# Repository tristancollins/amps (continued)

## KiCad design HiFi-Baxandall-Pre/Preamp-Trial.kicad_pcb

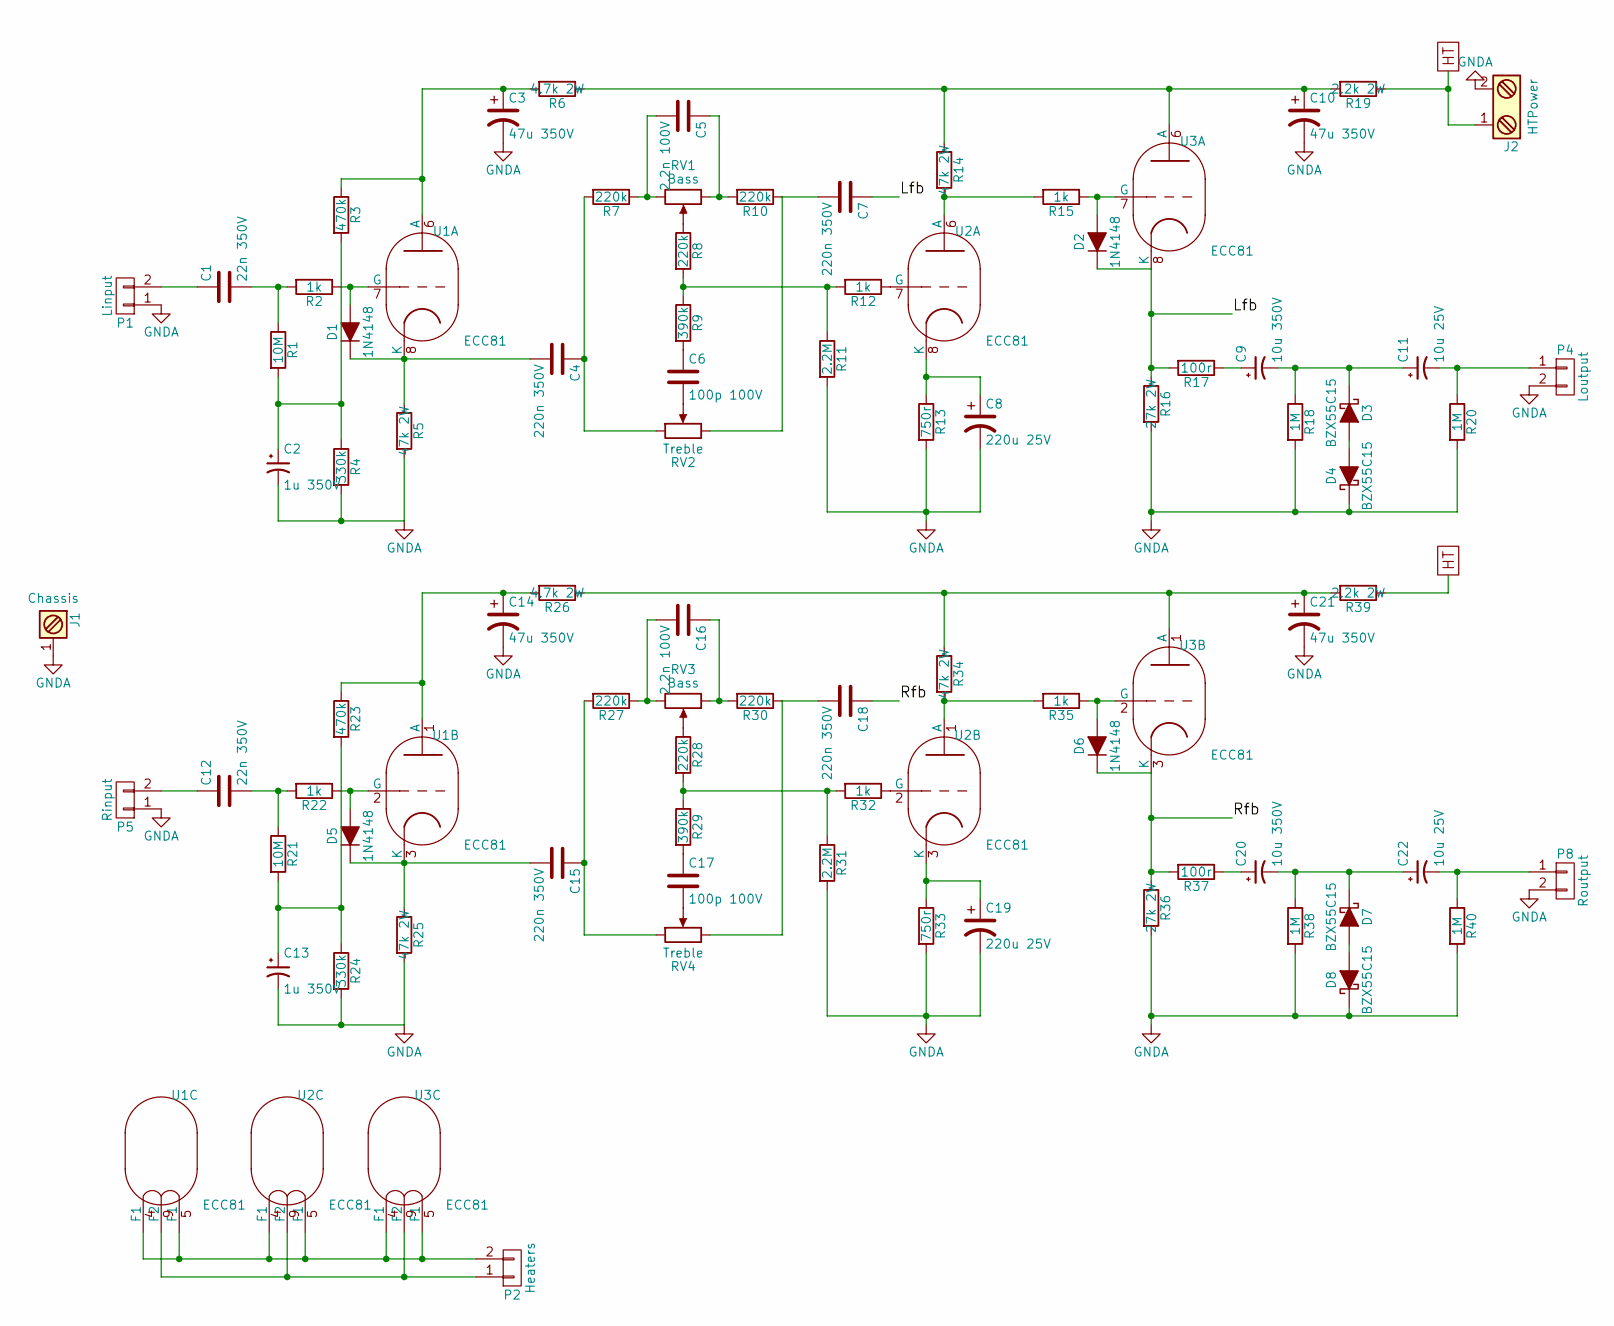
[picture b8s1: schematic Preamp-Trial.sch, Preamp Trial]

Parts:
C1, C12: 22n 350V; C_Rect_L10.3mm_W5.0mm_P7.50mm_MKS4
C2, C13: 1u 350V; CP_Radial_D12.5mm_P5.00mm
C3, C10, C14, C21: 47u 350V; CP_Radial_D16.0mm_P7.50mm
C4, C7, C15, C18: 220n 350V; C_Rect_L16.5mm_W5.0mm_P15.00mm_MKT
C5, C16: 2.2n 100V; C_Rect_L4.6mm_W5.5mm_P2.50mm_MKS02_FKP02
C6, C17: 100p 100V; C_Disc_D7.5_P5
C8, C19: 220u 25V; CP_Radial_D12.5mm_P5.00mm
C9, C20: 10u 350V; CP_Radial_D12.5mm_P5.00mm
C11, C22: 10u 25V; CP_Radial_D6.3mm_P2.50mm
D1, D2, D5, D6: 1N4148; D_DO-41_SOD81_P7.62mm_Horizontal
D3, D4, D7, D8: BZX55C15; D_DO-41_SOD81_P7.62mm_Horizontal
J1: Chassis; MountingHole_3.2mm_M3_Pad
J2: HTPower; SolderWirePad_2x_1-2mmDrill_TC
P1: Linput; SolderWirePad_2x_1-2mmDrill_TC
P2: Heaters; SolderWirePad_2x_1-2mmDrill_TC
P4: Loutput; SolderWirePad_2x_1-2mmDrill_TC
P5: Rinput; SolderWirePad_2x_1-2mmDrill_TC
P8: Routput; SolderWirePad_2x_1-2mmDrill_TC
R1, R21: 10M; R_Axial_DIN0411_L9.9mm_D3.6mm_P12.70mm_Horizontal
R2, R12, R15, R22, R32, R35: 1k; R_Axial_DIN0207_L6.3mm_D2.5mm_P7.62mm_Horizontal
R3, R23: 470k; R_Axial_DIN0411_L9.9mm_D3.6mm_P12.70mm_Horizontal
R4, R24: 330k; R_Axial_DIN0411_L9.9mm_D3.6mm_P12.70mm_Horizontal
R5, R14, R25, R34: 47k 2W; R_Axial_DIN0414_L11.9mm_D4.5mm_P15.24mm_Horizontal
R6, R26: 4.7k 2W; R_Axial_DIN0414_L11.9mm_D4.5mm_P15.24mm_Horizontal
R7, R8, R10, R27, R28, R30: 220k; R_Axial_DIN0411_L9.9mm_D3.6mm_P12.70mm_Horizontal
R9, R29: 390k; R_Axial_DIN0207_L6.3mm_D2.5mm_P7.62mm_Horizontal
R11, R31: 2.2M; R_Axial_DIN0207_L6.3mm_D2.5mm_P7.62mm_Horizontal
R13, R33: 750r; R_Axial_DIN0411_L9.9mm_D3.6mm_P12.70mm_Horizontal
R16, R36: 27k 2W; R_Axial_DIN0414_L11.9mm_D4.5mm_P15.24mm_Horizontal
R17, R37: 100r; R_Axial_DIN0411_L9.9mm_D3.6mm_P12.70mm_Horizontal
R18, R20, R38, R40: 1M; R_Axial_DIN0207_L6.3mm_D2.5mm_P7.62mm_Horizontal
R19, R39: 2.2k 2W; R_Axial_DIN0414_L11.9mm_D4.5mm_P15.24mm_Horizontal
RV1, RV3: Bass; Potentiometer_WirePads
RV2, RV4: Treble; Potentiometer_WirePads
U1, U2, U3: ECC81; VALVE-ECC-83-1-TC

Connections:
/Lfb: C7.1, D2.1 (K), R16.1, R17.2, U3.8 (K)
/Rfb: C18.1, D6.1 (K), R36.1, R37.2, U3.3 (K)
GNDA: C2.2, C3.2, C8.2, C10.2, C13.2, C14.2, C19.2, C21.2, D4.1 (K), D8.1 (K), J1.1, J2.2, P1.1, P4.2, P5.1, P8.2, R4.2, R5.2, R11.2, R13.2, R16.2, R18.2, R20.2, R24.2, R25.2, R31.2, R33.2, R36.2, R38.2, R40.2
HT: J2.1, R19.1, R39.1
unnamed: C1.1, P1.2
unnamed: C1.2, R1.1, R2.2
unnamed: C2.1, R1.2, R3.2, R4.1
unnamed: C3.1, R3.1, R6.2, U1.6 (A)
unnamed: C4.1, R7.2, RV2.1
unnamed: C4.2, D1.1 (K), R5.1, U1.8 (K)
unnamed: C5.1, R10.2, RV1.1
unnamed: C5.2, R7.1, RV1.3
unnamed: C6.1, R9.2
unnamed: C6.2, RV2.2
unnamed: C7.2, R10.1, RV2.3
unnamed: C8.1, R13.1, U2.8 (K)
unnamed: C9.1, R17.1
unnamed: C10.1, R6.1, R14.1, R19.2, U3.6 (A)
unnamed: C9.2, C11.1, D3.1 (K), R18.1
unnamed: C11.2, P4.1, R20.1
unnamed: C12.1, P5.2
unnamed: C12.2, R21.1, R22.2
unnamed: C13.1, R21.2, R23.2, R24.1
unnamed: C14.1, R23.1, R26.2, U1.1 (A)
unnamed: C15.1, R27.2, RV4.1
unnamed: C15.2, D5.1 (K), R25.1, U1.3 (K)
unnamed: C16.1, R30.2, RV3.1
unnamed: C16.2, R27.1, RV3.3
unnamed: C17.1, R29.2
unnamed: C17.2, RV4.2
unnamed: C18.2, R30.1, RV4.3
unnamed: C19.1, R33.1, U2.3 (K)
unnamed: C20.1, R37.1
unnamed: C20.2, C22.1, D7.1 (K), R38.1
unnamed: C21.1, R26.1, R34.1, R39.2, U3.1 (A)
unnamed: C22.2, P8.1, R40.1
unnamed: D1.2 (A), R2.1, U1.7 (G)
unnamed: D2.2 (A), R15.1, U3.7 (G)
unnamed: D3.2 (A), D4.2 (A)
unnamed: D5.2 (A), R22.1, U1.2 (G)
unnamed: D6.2 (A), R35.1, U3.2 (G)
unnamed: D7.2 (A), D8.2 (A)
unnamed: P2.1, U1.9 (F2), U2.9 (F2), U3.9 (F2)
unnamed: P2.2, U1.4 (F1), U1.5 (F1), U2.4 (F1), U2.5 (F1), U3.4 (F1), U3.5 (F1)
unnamed: R8.1, RV1.2
unnamed: R8.2, R9.1, R11.1, R12.2
unnamed: R12.1, U2.7 (G)
unnamed: R14.2, R15.2, U2.6 (A)
unnamed: R28.1, RV3.2
unnamed: R28.2, R29.1, R31.1, R32.2
unnamed: R32.1, U2.2 (G)
unnamed: R34.2, R35.2, U2.1 (A)

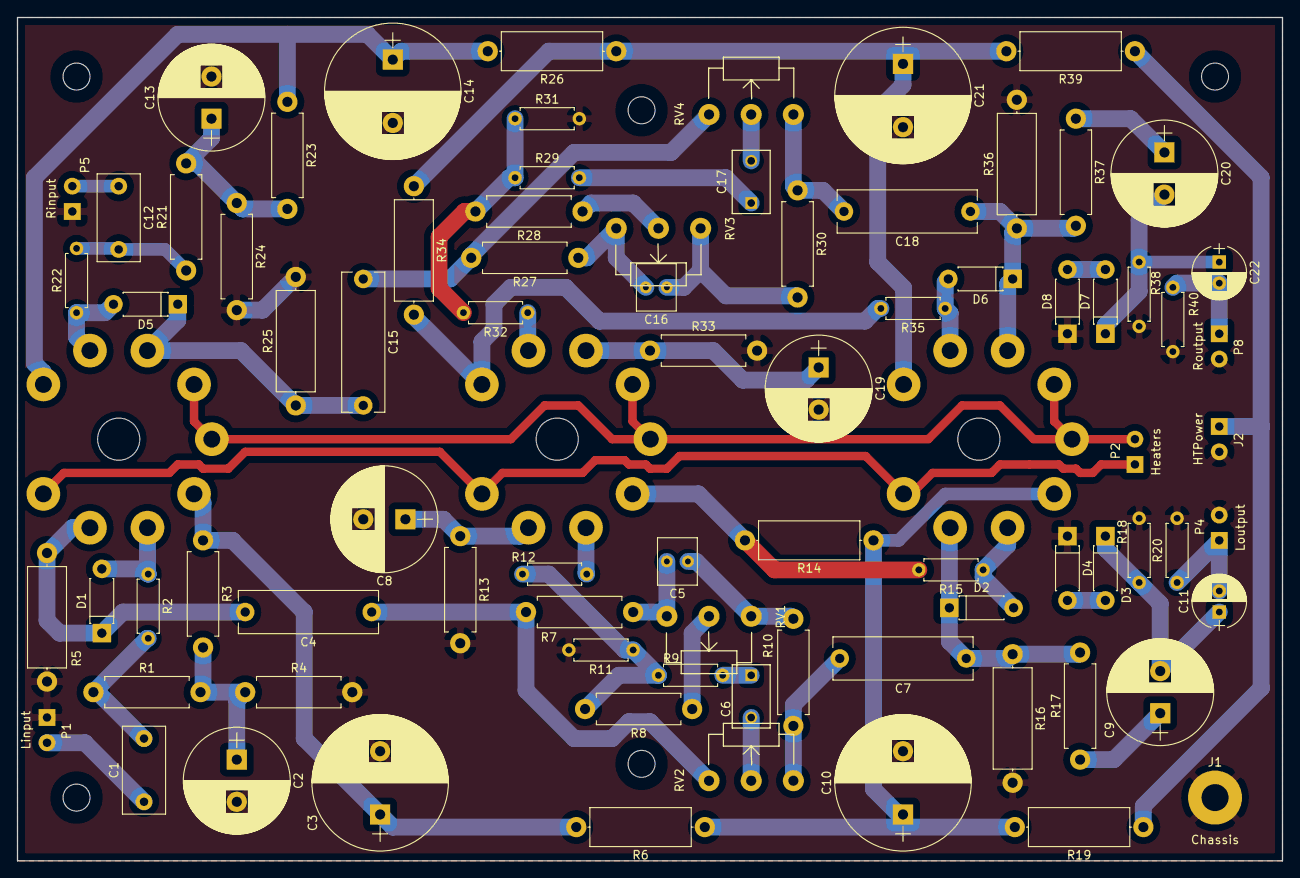
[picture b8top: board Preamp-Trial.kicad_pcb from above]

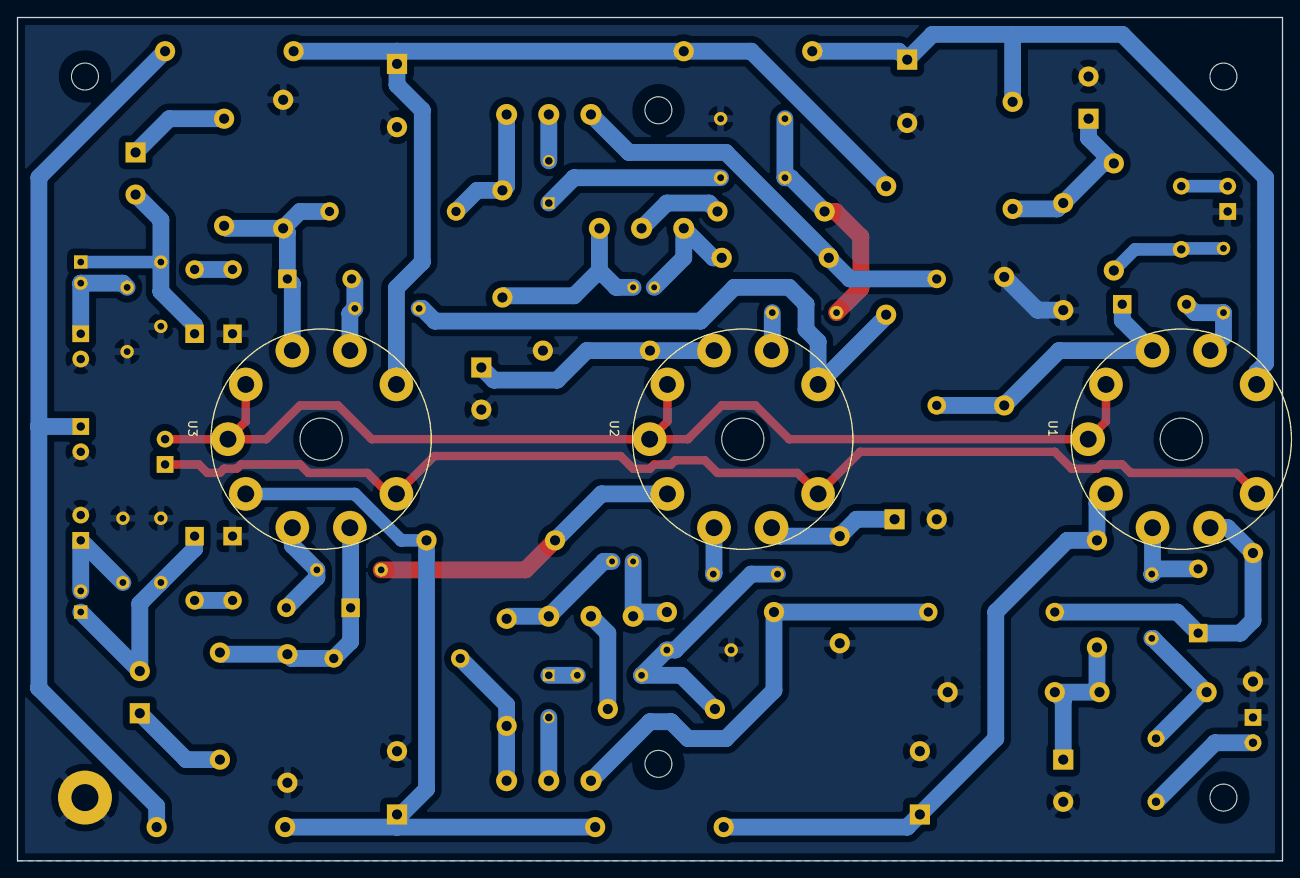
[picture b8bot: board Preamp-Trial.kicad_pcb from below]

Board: 2 copper layers, 150.0 x 100.0 mm, 84 parts (3 on the bottom side), 52 nets.

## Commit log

2020-04-26 readme altered
2020-04-26 1st upload of PCB files
2020-04-26 2nd upload of PCB files
2020-04-26 Removing SSFX old version
2020-04-26 Adding SSFX new version
2020-04-26 Adding HiFi PCBs
2020-04-26 Add Baxandall Preamp
2020-05-21 Added untested cathodyne and input PCBs
2020-06-13 Updating Cathodyne to be fixed bias
2020-09-13 adding reverb board gerbers
2020-09-13 adding RS-274X gerbers
2021-06-04 initial commit of BabyHuey
2021-06-04 adding .gitignore
2021-12-14 Change channel power filter node net
2021-12-14 heater routing start
2021-12-14 further heather routing
2021-12-14 updated C & D footprints
2021-12-15 Fix rescued symbols
2021-12-15 many updates to layout and schemo fix
2021-12-15 Initial shoddy routing and fixed error on schematic
2021-12-15 more routing
2021-12-18 adding uTracer ESP32 board design
2021-12-20 moving uTracer PCB to its own repo
2021-12-27 More routing, tidy up of edge cuts and mounting holes
2021-12-27 Pre-replicate commit. Text labels added
2021-12-27 layout replicated and routing tweaked
2021-12-29 move to v6 and huge changes
2021-12-29 more layout tweaks and tidying. v5 files deleted
2021-12-29 starting to fix DRC errors
2021-12-29 re-positioned resistor, passing DRC a bit better
2021-12-29 layout tweaks and adding net labels
2021-12-30 schematic corrections
2021-12-30 Moving BabyHuey to its own repo
2021-12-30 adding in guitar input select PCB
2021-12-31 upgrading power supply board to KiCADv6
2022-01-02 updated layouts and schemes
2022-01-07 update select pcb
2022-01-10 tweak
2022-01-15 updates and gerbers addtions
2022-02-25 updating 5V supply board
2022-02-25 updated 5V supply to stop brown-outs
2022-03-04 tidy tracks of power supply
2024-07-28 move HiFi designs to own repos
2024-07-28 moving guitar designs to own repos
